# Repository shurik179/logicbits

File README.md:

# Logic Gates Demonstration Kit

This directory contains files related to my Logic Gate Demonstraiton kit. This project is described in detail in my [Instructable](https://www.instructables.com/Logic-Gates-Demonstration-Kit/).

All files are released under MIT license; see LICENSE file in this directory for details.

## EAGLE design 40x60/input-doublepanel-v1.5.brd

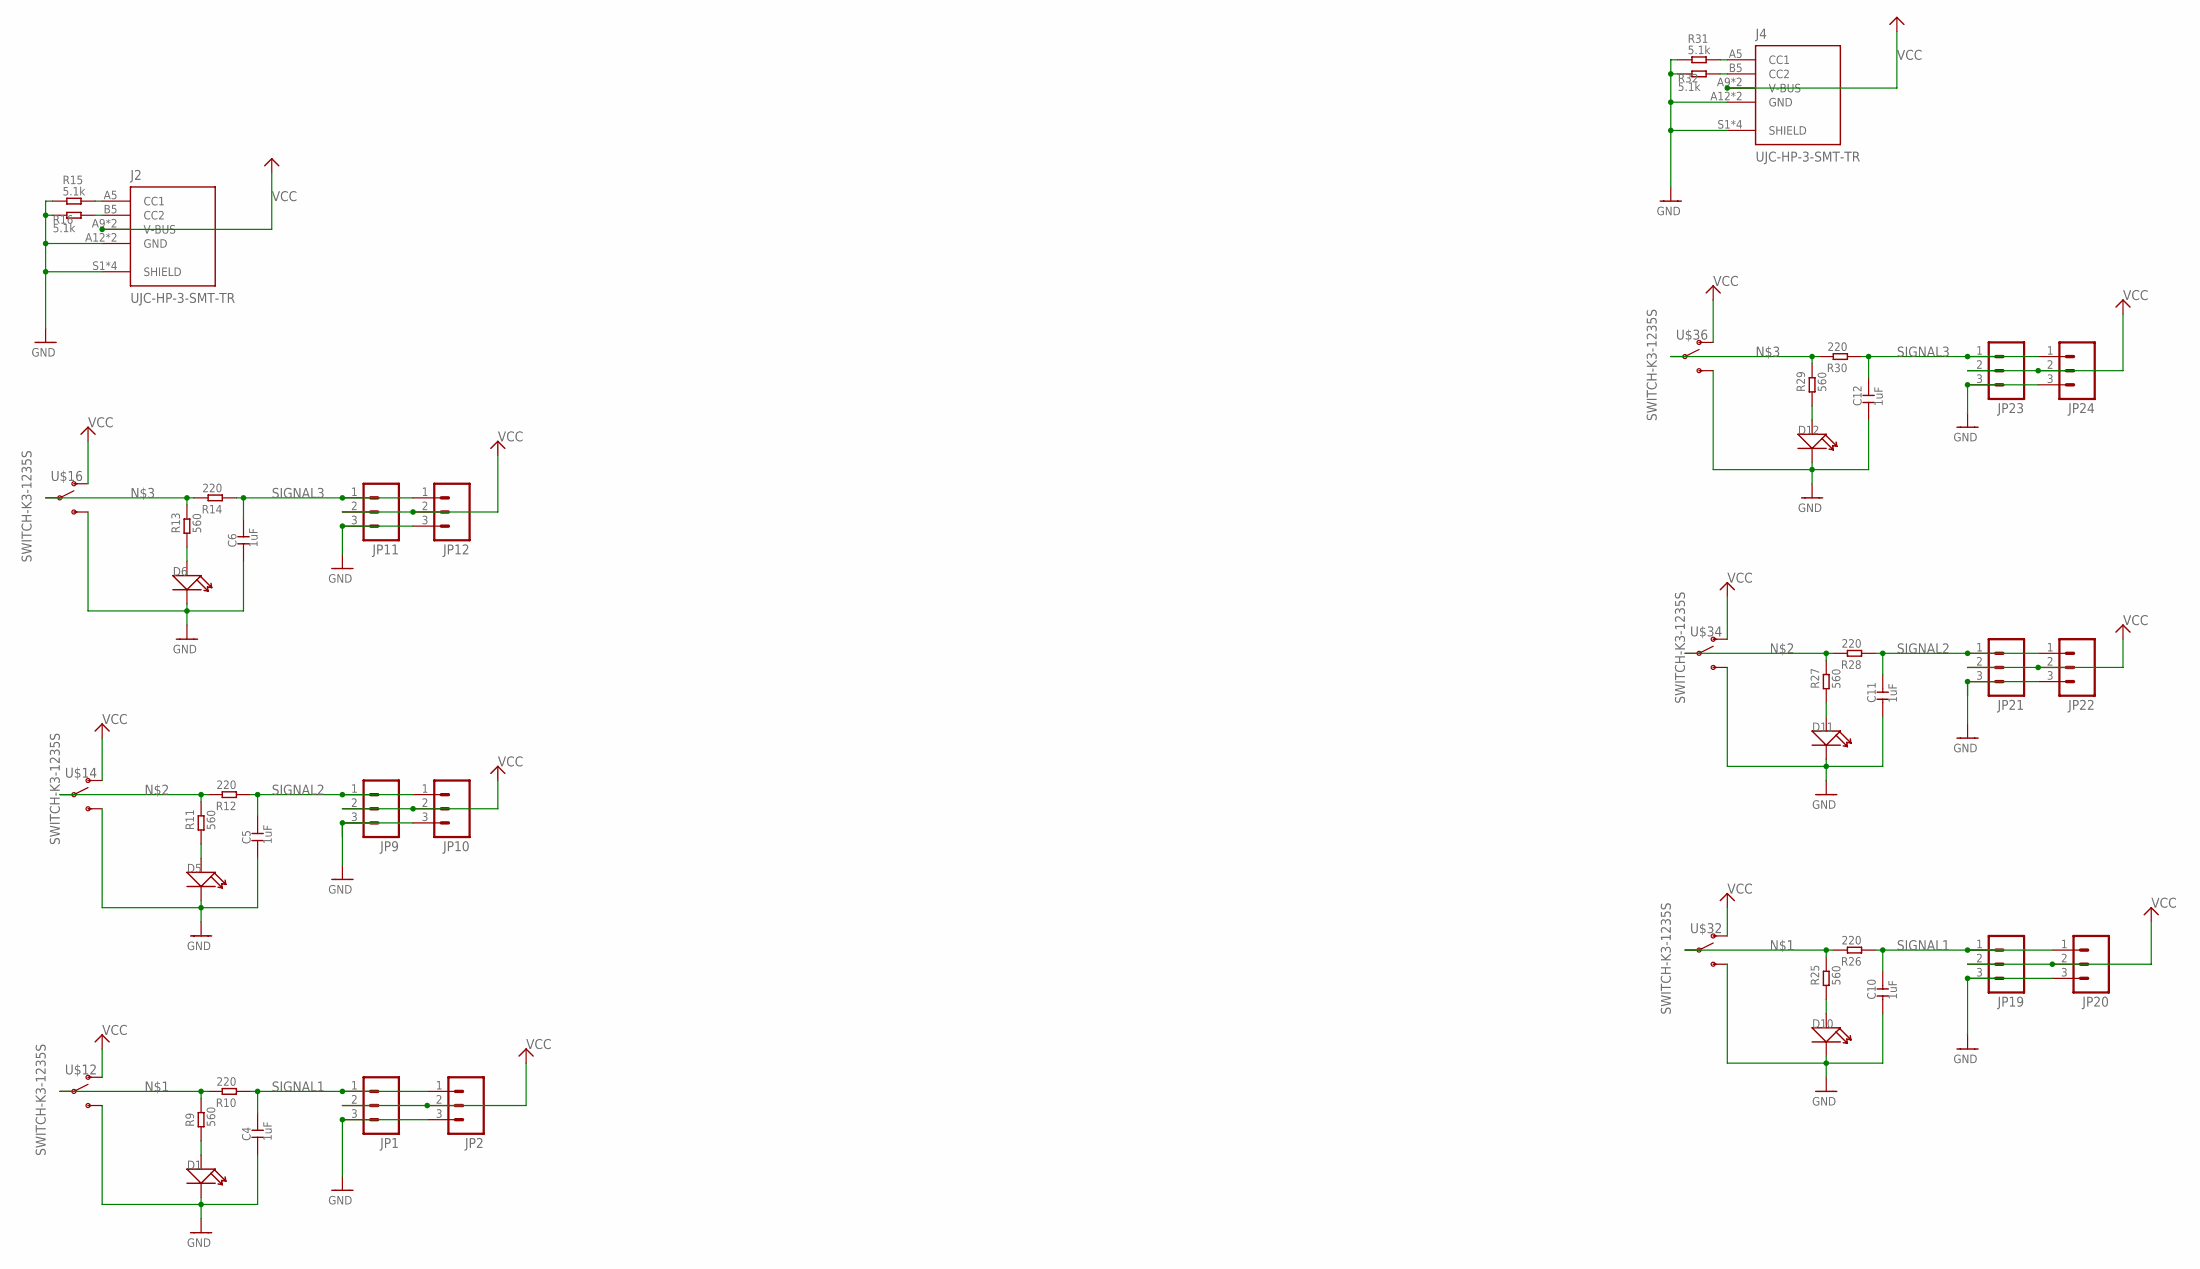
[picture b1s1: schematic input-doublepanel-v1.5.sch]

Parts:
C4, C5, C6, C10, C11, C12: 1uF; 0603
D1, D5, D6, D10, D11, D12: SMD-LED-0805; LED-0805
J2, J4: UJC-HP-3-SMT-TR; CUI_UJC-HP-3-SMT-TR
JP1, JP2, JP9, JP10, JP11, JP12, JP19, JP20, JP21, JP22, JP23, JP24: SPARKFUN_M031SMD-RA-MALE; SPARKFUN_1X03-SMD-MALE
R9, R11, R13, R25, R27, R29: 560; 0603
R10, R12, R14, R26, R28, R30: 220; 0603
R15, R16, R31, R32: 5.1k; 0603
U$12, U$14, U$16, U$32, U$34, U$36: SWITCH-K3-1235S

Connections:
GND: C4.1, C5.1, C6.1, C10.1, C11.1, C12.1, D1.-, D5.-, D6.-, D10.-, D11.-, D12.-, J2.A12 (GND), J2.B12 (GND), J2.S1 (SHIELD), J2.S2 (SHIELD), J2.S3 (SHIELD), J2.S4 (SHIELD), J4.A12 (GND), J4.B12 (GND), J4.S1 (SHIELD), J4.S2 (SHIELD), J4.S3 (SHIELD), J4.S4 (SHIELD), JP1.3, JP2.3, JP9.3, JP10.3, JP11.3, JP12.3, JP19.3, JP20.3, JP21.3, JP22.3, JP23.3, JP24.3, R15.1, R16.1, R31.1, R32.1, U$12.P$3 (S), U$14.P$3 (S), U$16.P$3 (S), U$32.P$3 (S), U$34.P$3 (S), U$36.P$3 (S)
unnamed: D5.+, R9.2, R10.2, R11.1, R25.2, R26.2, U$12.P$2, U$32.P$2
unnamed: D1.+, R9.1, R11.2, R12.2, R27.2, R28.2, U$14.P$2, U$34.P$2
unnamed: D6.+, R13.1, R13.2, R14.2, R29.2, R30.2, U$16.P$2, U$36.P$2
unnamed: J2.A5 (CC1), R15.2
unnamed: J2.B5 (CC2), R16.2
unnamed: D11.+, R27.1
unnamed: D10.+, R25.1
unnamed: D12.+, R29.1
unnamed: J4.A5 (CC1), R31.2
unnamed: J4.B5 (CC2), R32.2
SIGNAL1: C4.2, C10.2, JP1.1, JP2.1, JP19.1, JP20.1, R10.1, R26.1
SIGNAL2: C5.2, C11.2, JP9.1, JP10.1, JP21.1, JP22.1, R12.1, R28.1
SIGNAL3: C6.2, C12.2, JP11.1, JP12.1, JP23.1, JP24.1, R14.1, R30.1
VCC: J2.A9 (V-BUS), J2.B9 (V-BUS), J4.A9 (V-BUS), J4.B9 (V-BUS), JP1.2, JP2.2, JP9.2, JP10.2, JP11.2, JP12.2, JP19.2, JP20.2, JP21.2, JP22.2, JP23.2, JP24.2, U$12.P$1 (O), U$14.P$1 (O), U$16.P$1 (O), U$32.P$1 (O), U$34.P$1 (O), U$36.P$1 (O)

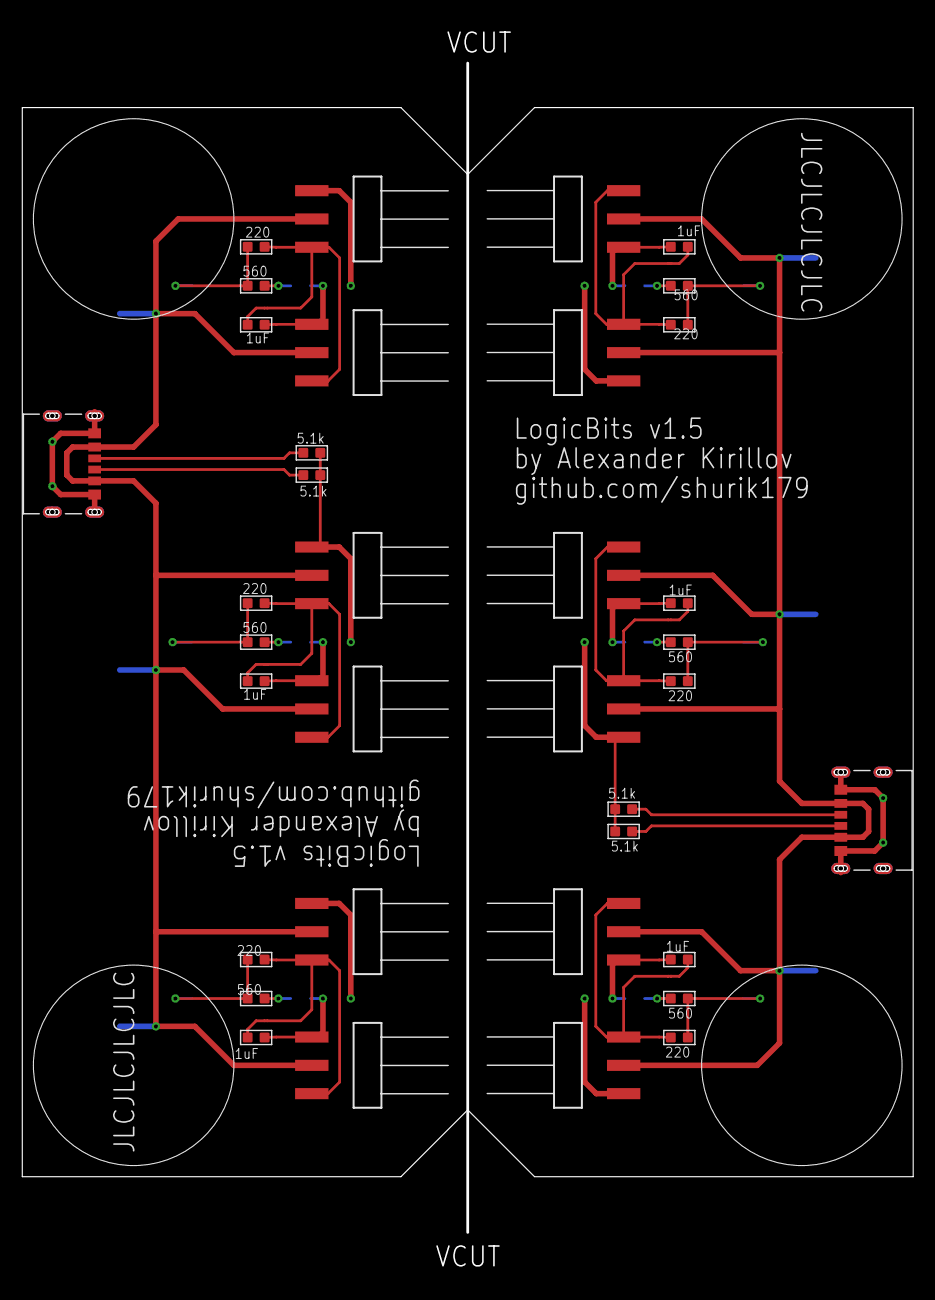
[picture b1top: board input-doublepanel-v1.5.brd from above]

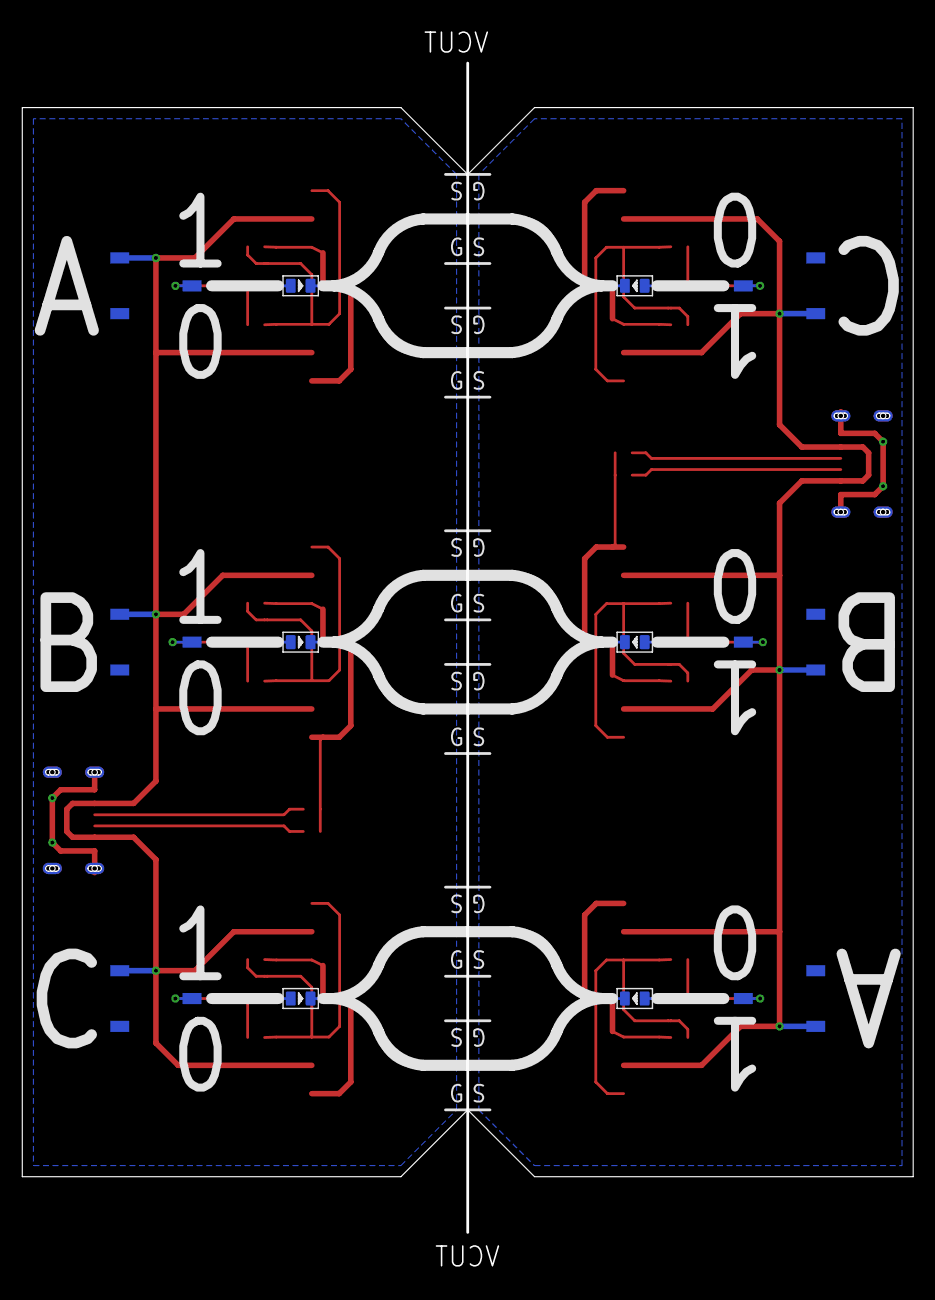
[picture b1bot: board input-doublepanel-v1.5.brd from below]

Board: 2 copper layers, 80.0 x 105.0 mm, 48 parts (12 on the bottom side), 15 nets.

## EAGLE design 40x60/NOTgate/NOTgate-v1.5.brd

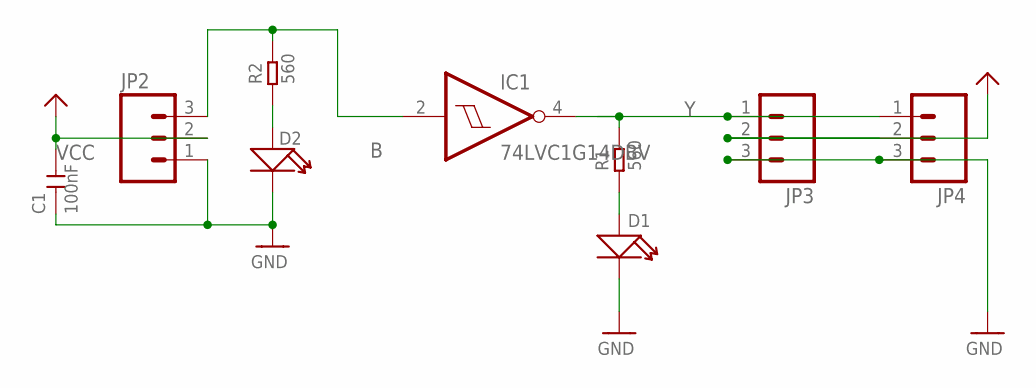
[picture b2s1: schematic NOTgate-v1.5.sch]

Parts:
C1: 100nF; 0603
D1, D2: SMD-LED-0805; LED-0805
IC1: 74LVC1G14DBV; SOT23-5
JP2, JP3, JP4: SPARKFUN_M031SMD-RA-MALE; SPARKFUN_1X03-SMD-MALE
R1, R2: 560; 0603

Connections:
B: IC1.2 (I), JP2.3, R2.2
GND: C1.1, D1.-, D2.-, IC1.3 (GND), JP2.1, JP3.3, JP4.3
unnamed: D2.+, R2.1
unnamed: D1.+, R1.1
VCC: C1.2, IC1.5 (VCC), JP2.2, JP3.2, JP4.2
Y: IC1.4 (O), JP3.1, JP4.1, R1.2

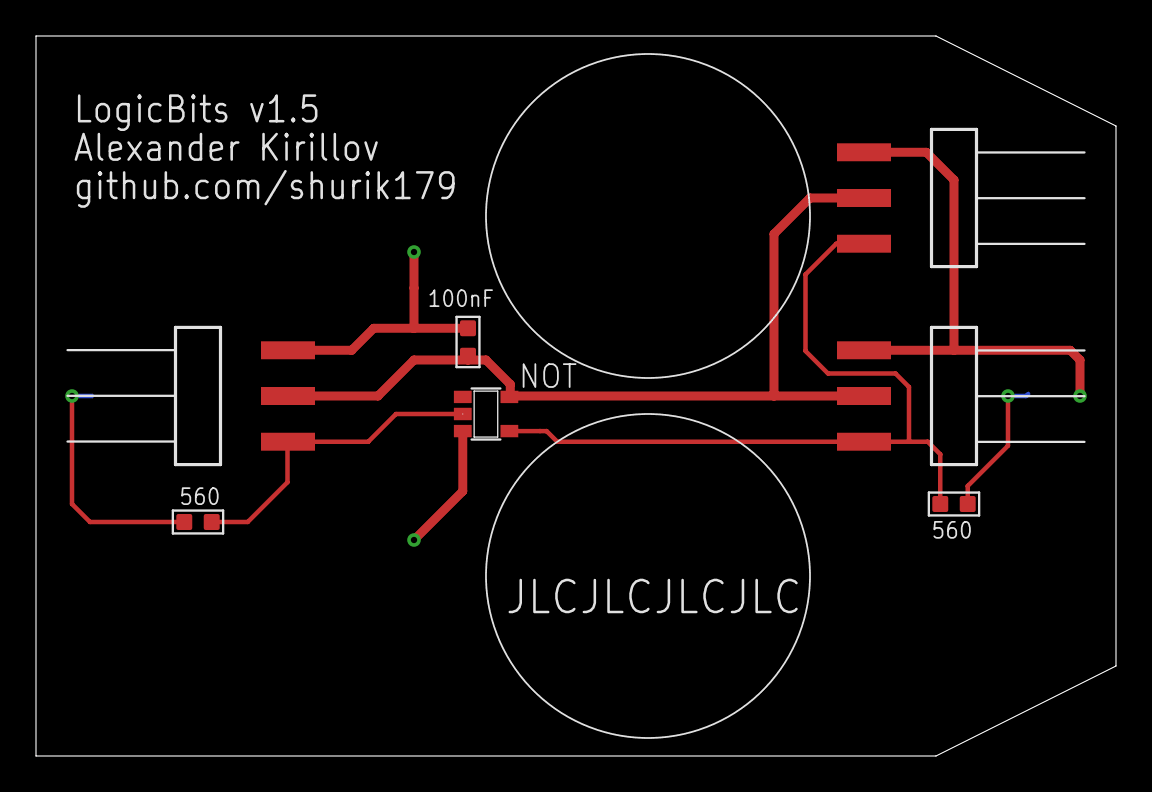
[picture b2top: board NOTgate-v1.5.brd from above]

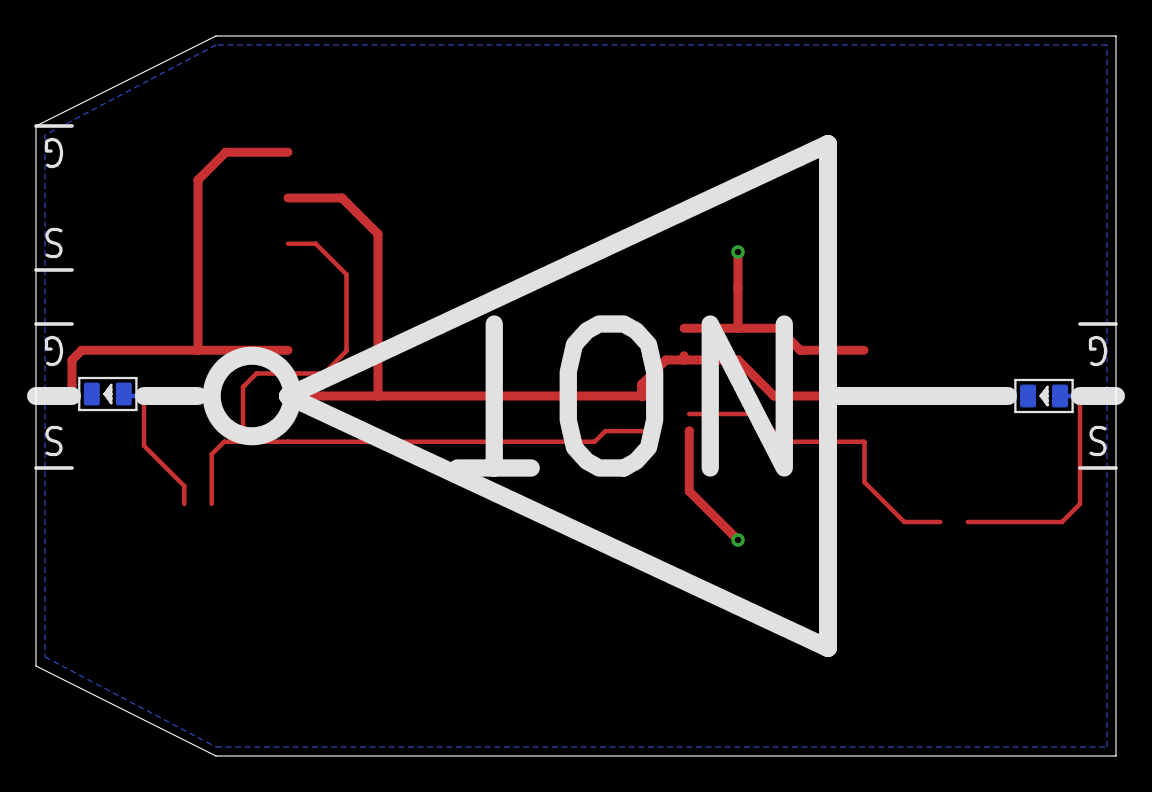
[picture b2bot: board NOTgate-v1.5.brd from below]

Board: 2 copper layers, 60.0 x 40.0 mm, 9 parts (2 on the bottom side), 6 nets.

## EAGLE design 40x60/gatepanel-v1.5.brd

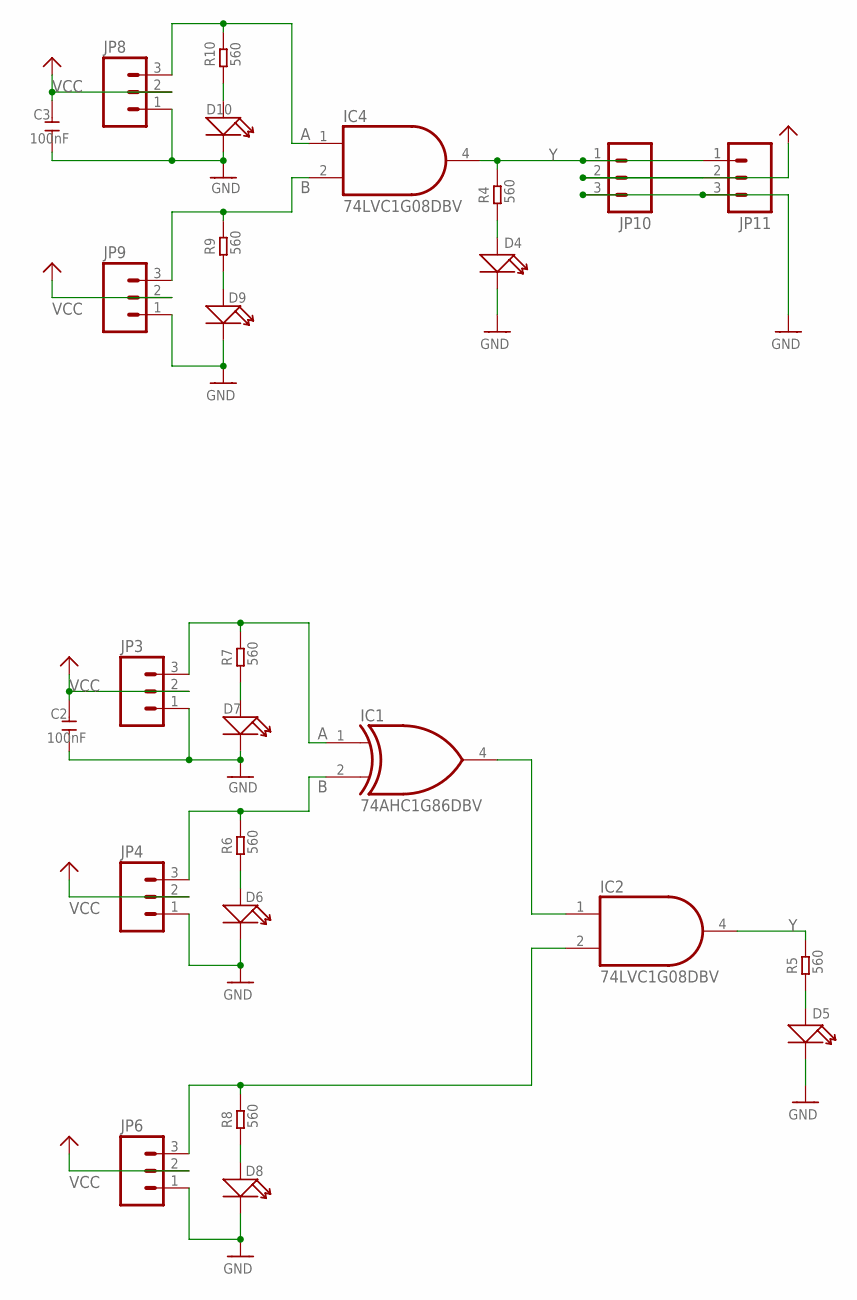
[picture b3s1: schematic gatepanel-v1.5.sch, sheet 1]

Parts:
C2, C3: 100nF; 0603
D4, D5, D6, D7, D8, D9, D10: SMD-LED-0805; LED-0805
IC1: 74AHC1G86DBV; SOT23-5
IC2, IC4: 74LVC1G08DBV; SOT23-5
JP3, JP4, JP6, JP8, JP9, JP10, JP11: SPARKFUN_M031SMD-RA-MALE; SPARKFUN_1X03-SMD-MALE
R4, R5, R6, R7, R8, R9, R10: 560; 0603

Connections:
A: IC1.1 (I0), IC4.1 (I0), JP3.3, JP8.3, R7.2, R10.2; also elsewhere on the board
B: IC1.2 (I1), IC4.2 (I1), JP4.3, JP9.3, R6.2, R9.2; also elsewhere on the board
B2: IC2.2 (I1), JP6.3, R8.2
GND: C2.1, C3.1, D4.-, D5.-, D6.-, D7.-, D8.-, D9.-, D10.-, IC1.3 (GND), IC2.3 (GND), IC4.3 (GND), JP3.1, JP4.1, JP6.1, JP8.1, JP9.1, JP10.3, JP11.3; also elsewhere on the board
unnamed: D4.+, R4.1
unnamed: D9.+, R9.1
unnamed: D10.+, R10.1
unnamed: D5.+, R5.1
unnamed: D6.+, R6.1
unnamed: D7.+, R7.1
unnamed: D8.+, R8.1
unnamed: IC1.4 (O), IC2.1 (I0)
VCC: C2.2, C3.2, IC1.5 (VCC), IC2.5 (VCC), IC4.5 (VCC), JP3.2, JP4.2, JP6.2, JP8.2, JP9.2, JP10.2, JP11.2; also elsewhere on the board
Y: IC2.4 (O), IC4.4 (O), JP10.1, JP11.1, R4.2, R5.2; also elsewhere on the board

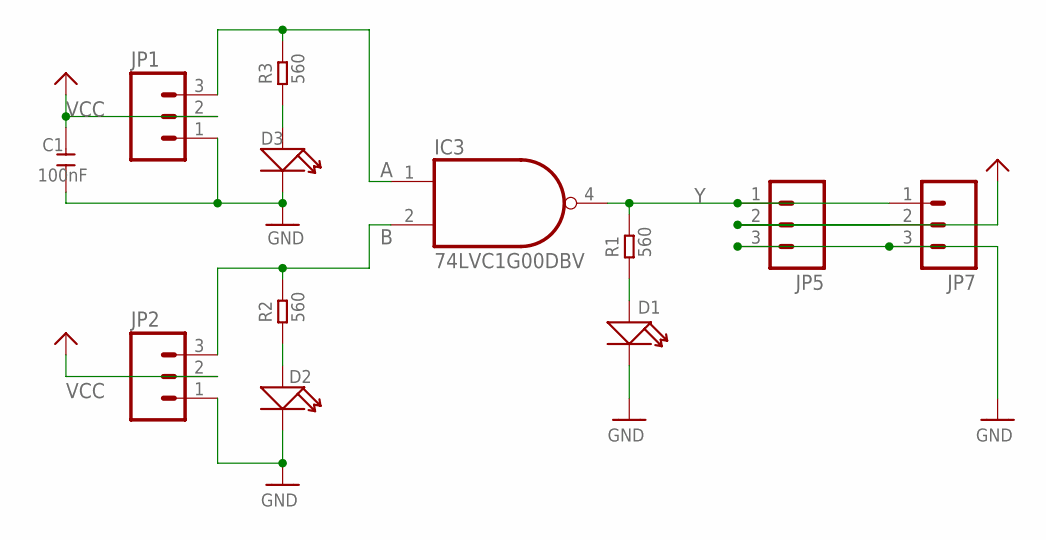
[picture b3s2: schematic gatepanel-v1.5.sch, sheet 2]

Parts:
C1: 100nF; 0603
D1, D2, D3: SMD-LED-0805; LED-0805
IC3: 74LVC1G00DBV; SOT23-5
JP1, JP2, JP5, JP7: SPARKFUN_M031SMD-RA-MALE; SPARKFUN_1X03-SMD-MALE
R1, R2, R3: 560; 0603

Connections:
A: IC3.1 (I0), JP1.3, R3.2; also elsewhere on the board
B: IC3.2 (I1), JP2.3, R2.2; also elsewhere on the board
GND: C1.1, D1.-, D2.-, D3.-, IC3.3 (GND), JP1.1, JP2.1, JP5.3, JP7.3; also elsewhere on the board
unnamed: D2.+, R2.1
unnamed: D3.+, R3.1
unnamed: D1.+, R1.1
VCC: C1.2, IC3.5 (VCC), JP1.2, JP2.2, JP5.2, JP7.2; also elsewhere on the board
Y: IC3.4 (O), JP5.1, JP7.1, R1.2; also elsewhere on the board

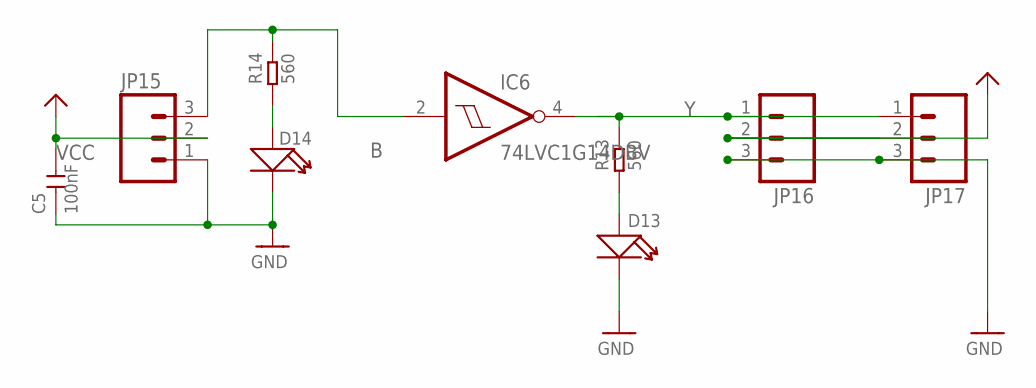
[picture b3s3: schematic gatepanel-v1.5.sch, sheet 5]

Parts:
C5: 100nF; 0603
D13, D14: SMD-LED-0805; LED-0805
IC6: 74LVC1G14DBV; SOT23-5
JP15, JP16, JP17: SPARKFUN_M031SMD-RA-MALE; SPARKFUN_1X03-SMD-MALE
R13, R14: 560; 0603

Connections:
B: IC6.2 (I), JP15.3, R14.2; also elsewhere on the board
GND: C5.1, D13.-, D14.-, IC6.3 (GND), JP15.1, JP16.3, JP17.3; also elsewhere on the board
unnamed: D13.+, R13.1
unnamed: D14.+, R14.1
VCC: C5.2, IC6.5 (VCC), JP15.2, JP16.2, JP17.2; also elsewhere on the board
Y: IC6.4 (O), JP16.1, JP17.1, R13.2; also elsewhere on the board

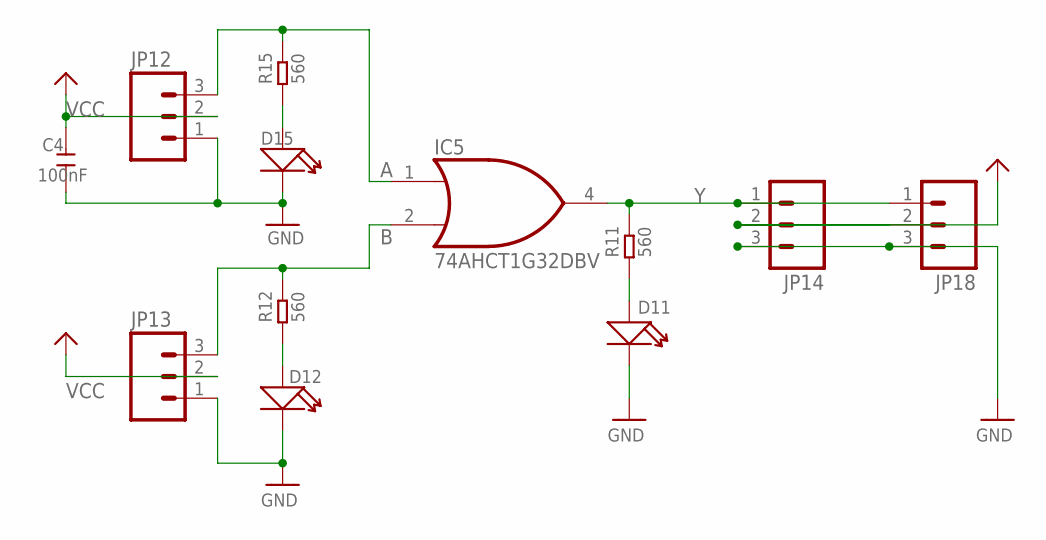
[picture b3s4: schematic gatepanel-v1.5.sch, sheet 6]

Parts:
C4: 100nF; 0603
D11, D12, D15: SMD-LED-0805; LED-0805
IC5: 74AHCT1G32DBV; SOT23-5
JP12, JP13, JP14, JP18: SPARKFUN_M031SMD-RA-MALE; SPARKFUN_1X03-SMD-MALE
R11, R12, R15: 560; 0603

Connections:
A: IC5.1 (I0), JP12.3, R15.2; also elsewhere on the board
B: IC5.2 (I1), JP13.3, R12.2; also elsewhere on the board
GND: C4.1, D11.-, D12.-, D15.-, IC5.3 (GND), JP12.1, JP13.1, JP14.3, JP18.3; also elsewhere on the board
unnamed: D11.+, R11.1
unnamed: D12.+, R12.1
unnamed: D15.+, R15.1
VCC: C4.2, IC5.5 (VCC), JP12.2, JP13.2, JP14.2, JP18.2; also elsewhere on the board
Y: IC5.4 (O), JP14.1, JP18.1, R11.2; also elsewhere on the board

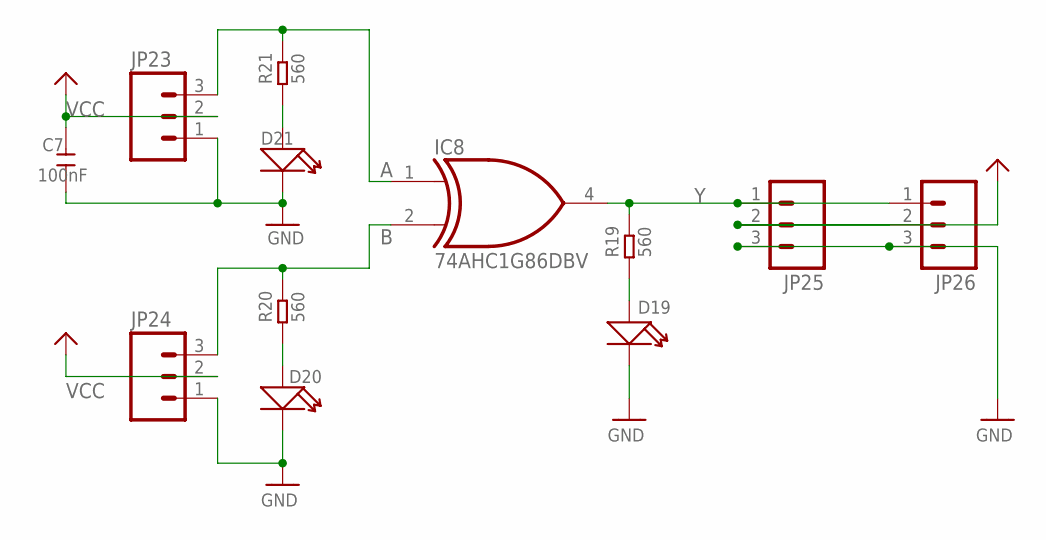
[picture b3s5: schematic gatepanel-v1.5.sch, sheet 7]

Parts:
C7: 100nF; 0603
D19, D20, D21: SMD-LED-0805; LED-0805
IC8: 74AHC1G86DBV; SOT23-5
JP23, JP24, JP25, JP26: SPARKFUN_M031SMD-RA-MALE; SPARKFUN_1X03-SMD-MALE
R19, R20, R21: 560; 0603

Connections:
A: IC8.1 (I0), JP23.3, R21.2; also elsewhere on the board
B: IC8.2 (I1), JP24.3, R20.2; also elsewhere on the board
GND: C7.1, D19.-, D20.-, D21.-, IC8.3 (GND), JP23.1, JP24.1, JP25.3, JP26.3; also elsewhere on the board
unnamed: D19.+, R19.1
unnamed: D20.+, R20.1
unnamed: D21.+, R21.1
VCC: C7.2, IC8.5 (VCC), JP23.2, JP24.2, JP25.2, JP26.2; also elsewhere on the board
Y: IC8.4 (O), JP25.1, JP26.1, R19.2; also elsewhere on the board

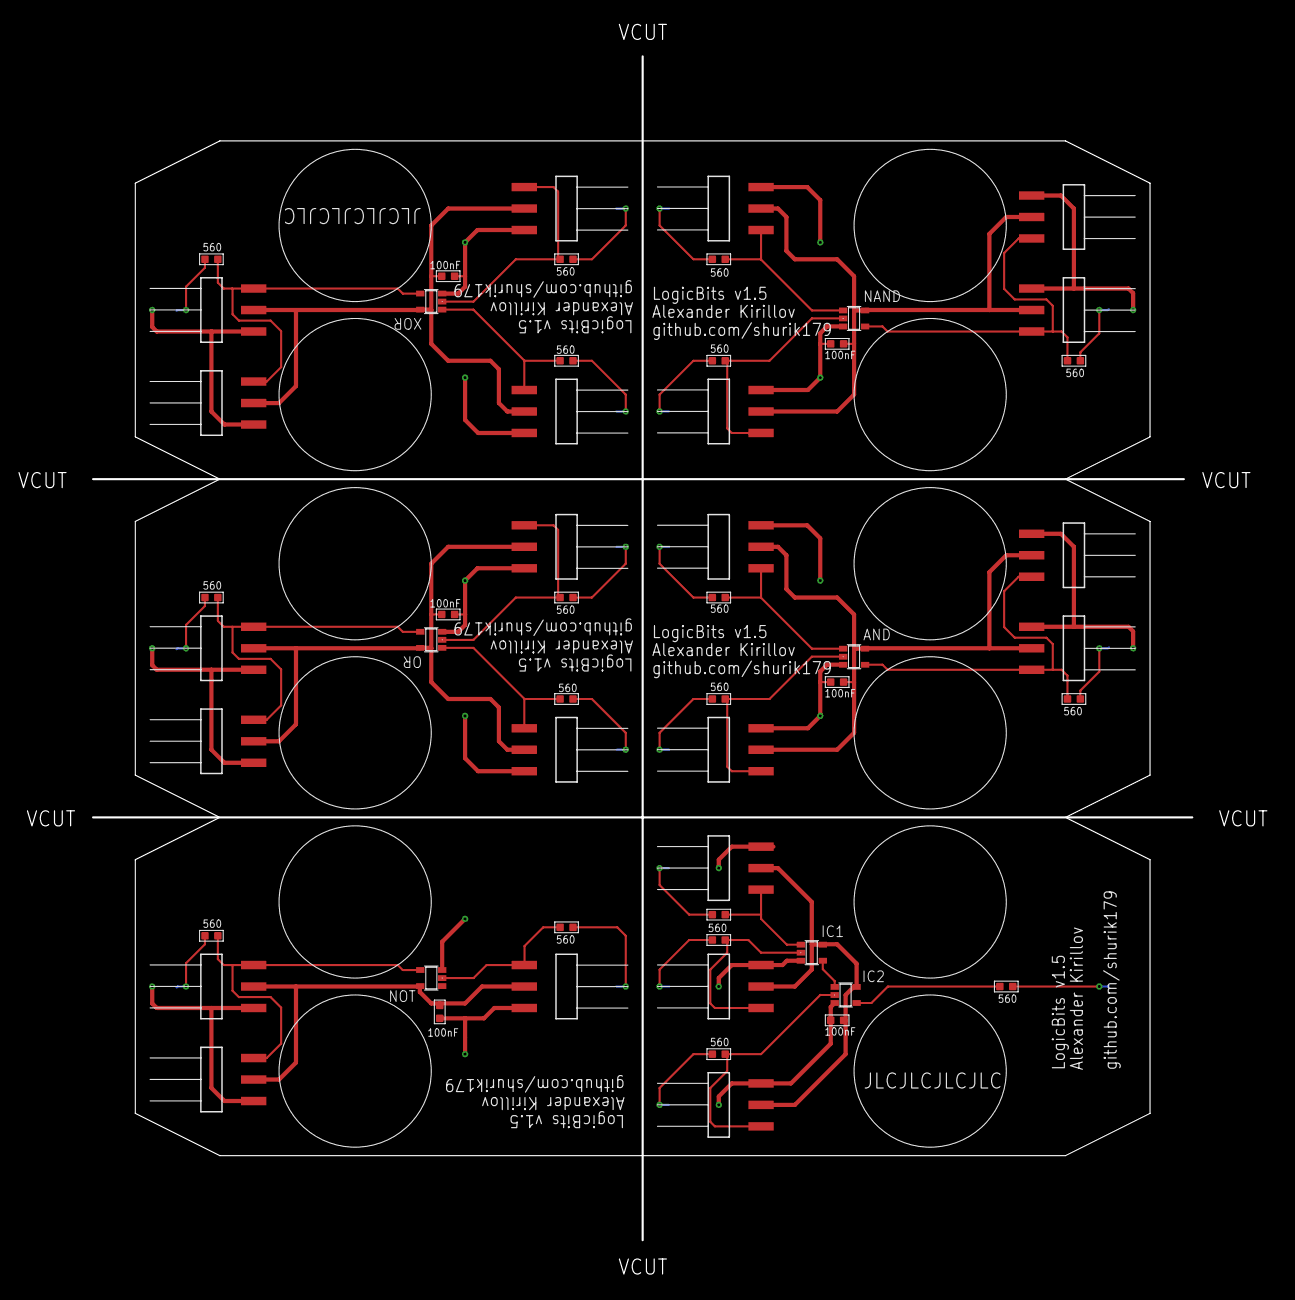
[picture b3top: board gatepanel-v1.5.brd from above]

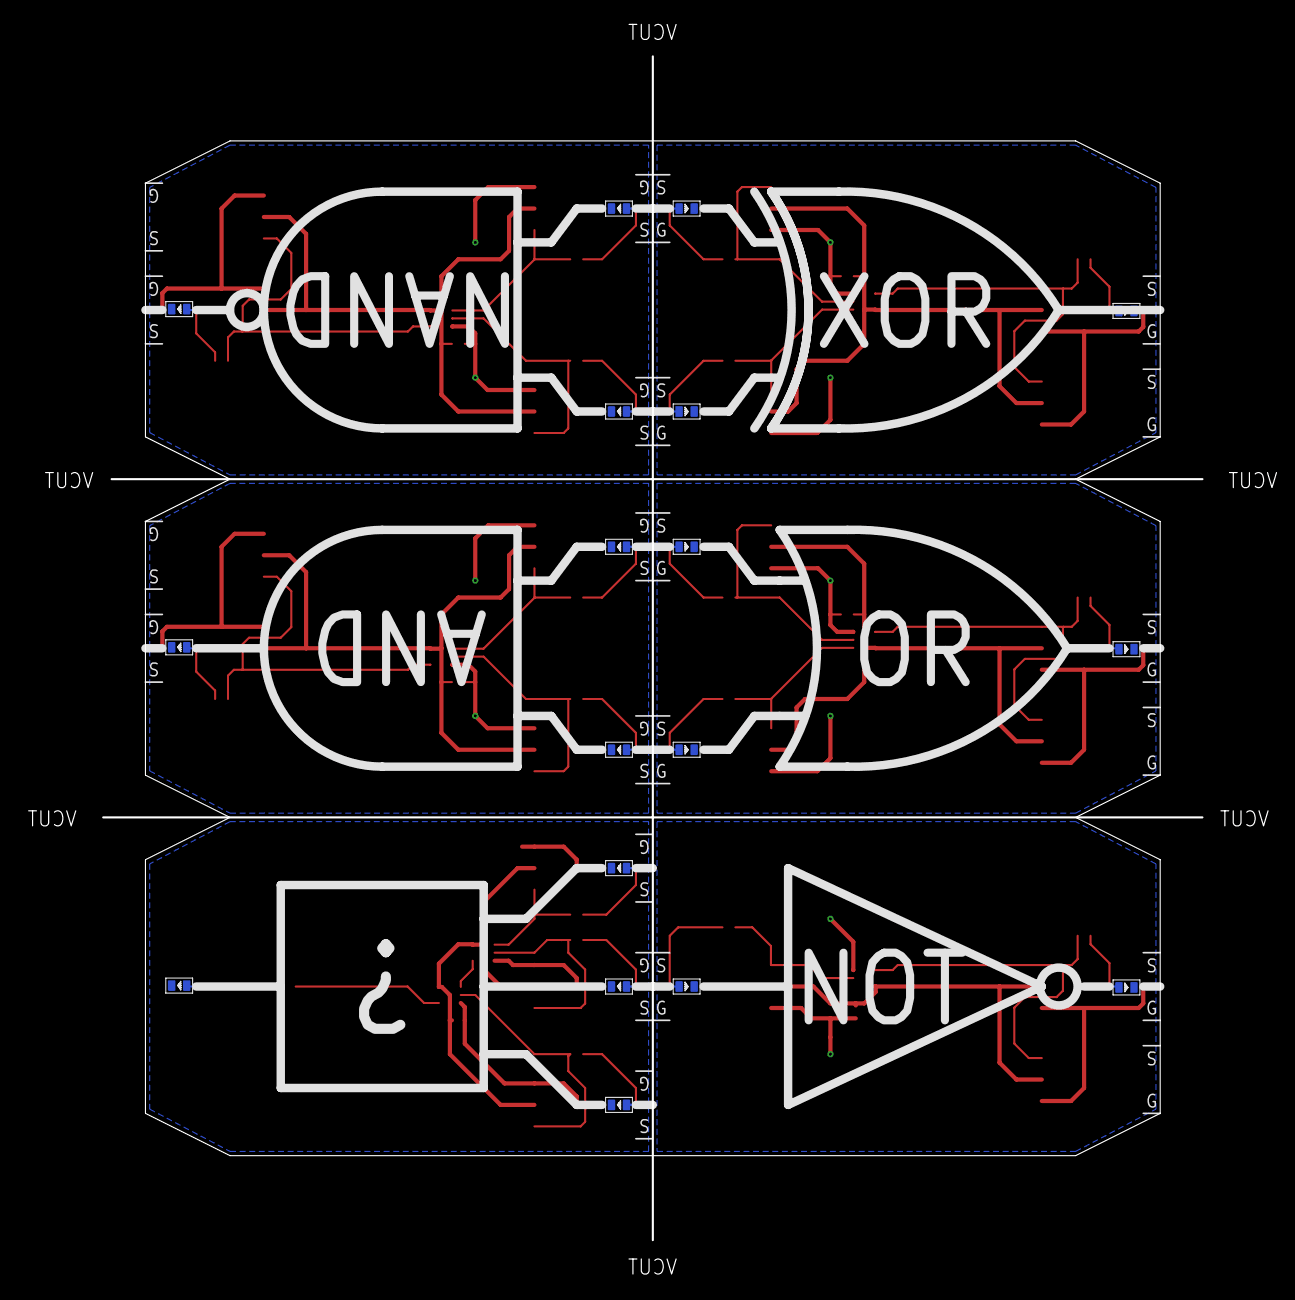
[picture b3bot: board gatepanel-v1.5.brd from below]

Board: 2 copper layers, 120.0 x 120.0 mm, 71 parts (18 on the bottom side), 25 nets.

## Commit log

2021-01-13 Initial upload
2021-01-13 updated input panel
2021-01-18 updated for v1.3
2021-01-19 Updating README
2021-01-19 Fixing image link
2025-05-10 updating for v2.0
2025-05-12 reorganization
